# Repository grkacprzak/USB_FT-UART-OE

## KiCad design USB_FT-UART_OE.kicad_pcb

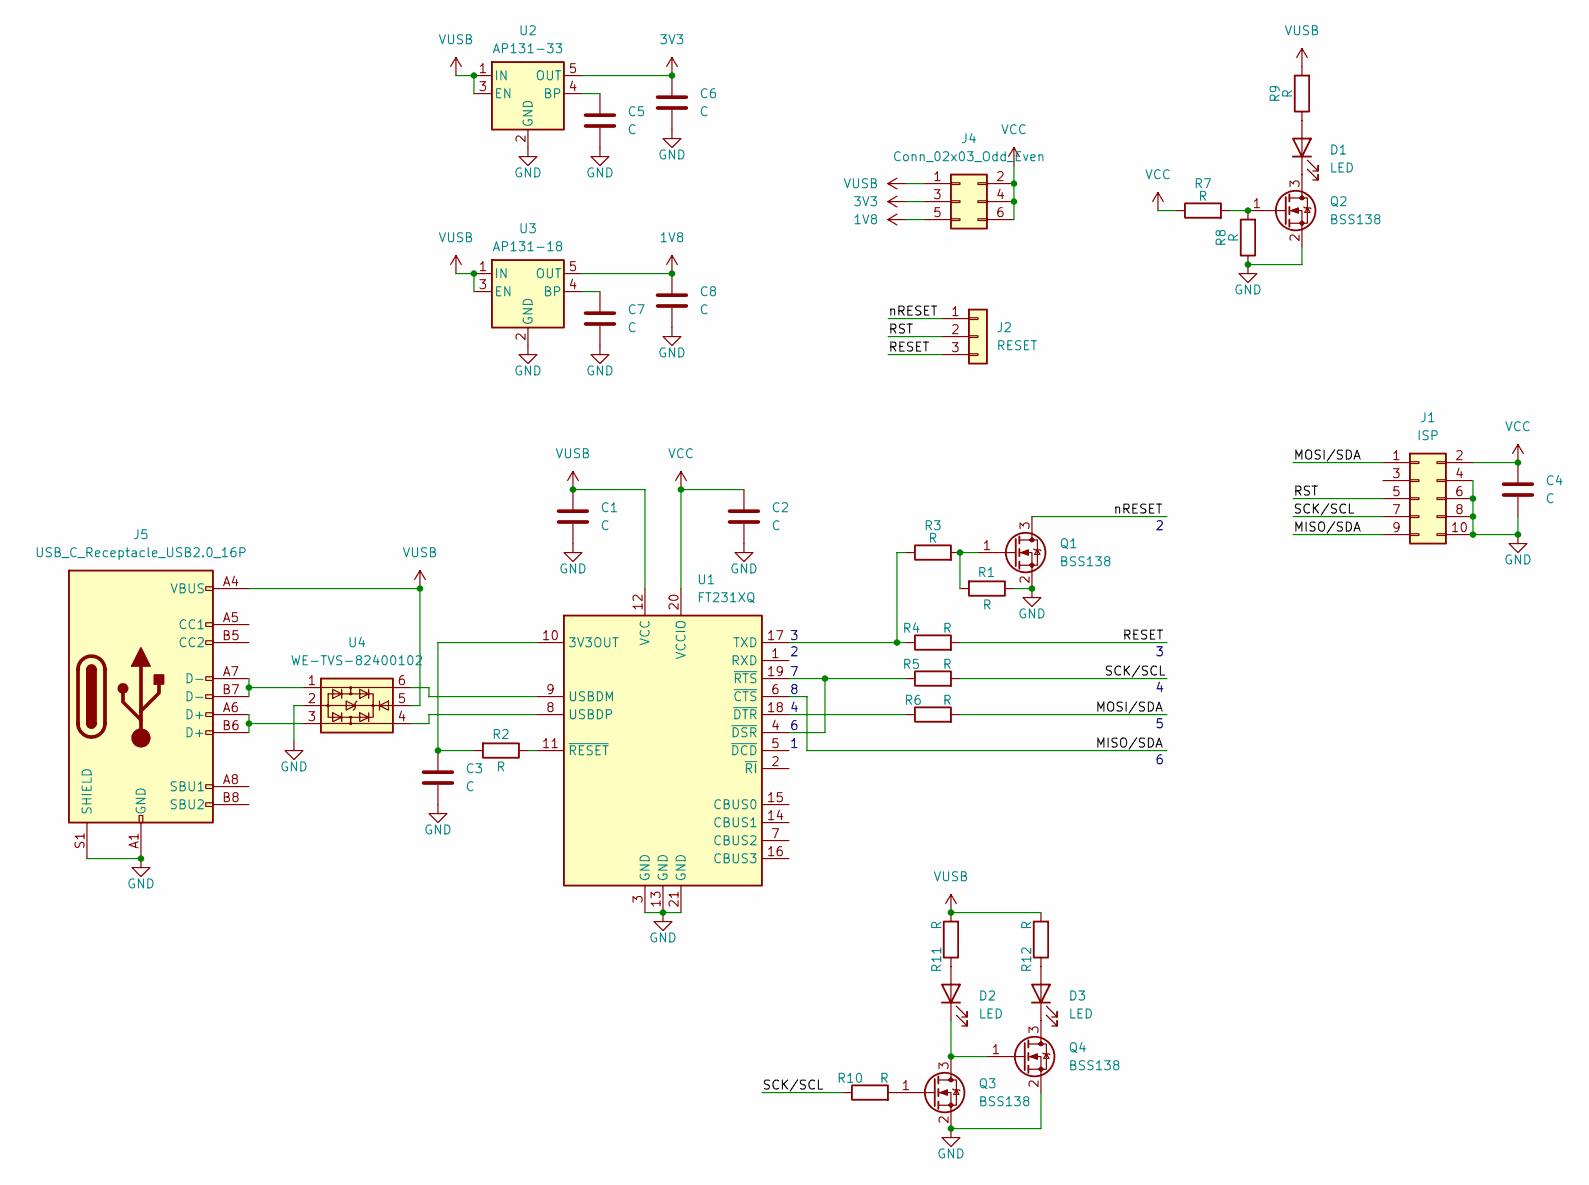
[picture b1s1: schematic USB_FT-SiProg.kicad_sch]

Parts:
C1, C2, C3, C4, C5, C6, C7, C8: C; C_0603_1608Metric
D1, D2, D3: LED; LED_0603_1608Metric
J1: ISP; IDC-Header_2x05_P2.54mm_EDGE
J2: RESET; PinHeader_1x03_P2.54mm_Vertical
J4: Conn_02x03_Odd_Even; PinHeader_2x03_P2.54mm_Vertical
J5: USB_C_Receptacle_USB2.0_16P; USB_C_Receptacle_Wuerth_629722000214
Q1, Q2, Q3, Q4: BSS138; SOT-23
R1, R2, R3, R4, R5, R6, R7, R8, R9, R10, R11, R12: R; R_0603_1608Metric
U1: FT231XQ; QFN-20-1EP_4x4mm_P0.5mm_EP2.5x2.5mm
U2: AP131-33; SOT-23-5
U3: AP131-18; SOT-23-5
U4: WE-TVS-82400102; SOT-23-6

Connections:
1V8: C8.1, J4.5, U3.5 (OUT)
3V3: C6.1, J4.3, U2.5 (OUT)
/MISO/SDA: J1.9, U1.6 (~CTS)
/MOSI/SDA: J1.1, R6.2
/RESET: J2.3, R4.2
/RST: J1.5, J2.2
/SCK/SCL: J1.7, R5.2, R10.1
/nRESET: J2.1, Q1.3 (D)
GND: C1.2, C2.2, C3.2, C4.2, C5.2, C6.2, C7.2, C8.2, J1.4, J1.6, J1.8, J1.10, J5.A1 (GND), J5.A12 (GND), J5.B1 (GND), J5.B12 (GND), J5.S1 (SHIELD), Q1.2 (S), Q2.2 (S), Q3.2 (S), Q4.2 (S), R1.1, R8.1, U1.3 (GND), U1.13 (GND), U1.21 (GND), U2.2 (GND), U3.2 (GND), U4.2
unnamed: D1.2 (A), R9.1
unnamed: D1.1 (K), Q2.3 (D)
unnamed: D2.2 (A), R11.1
unnamed: D2.1 (K), Q3.3 (D), Q4.1 (G)
unnamed: D3.2 (A), R12.1
unnamed: D3.1 (K), Q4.3 (D)
unnamed: J5.A6 (D+), J5.B6 (D+), U4.3
unnamed: J5.A7 (D-), J5.B7 (D-), U4.1
unnamed: Q1.1 (G), R1.2, R3.2
unnamed: Q2.1 (G), R7.2, R8.2
unnamed: Q3.1 (G), R10.2
unnamed: C3.1, R2.2, U1.10 (3V3OUT)
unnamed: R3.1, R4.1, U1.17 (TXD)
unnamed: U1.9 (USBDM), U4.6
unnamed: U1.8 (USBDP), U4.4
unnamed: R5.1, U1.4 (~DSR), U1.19 (~RTS)
unnamed: R6.1, U1.18 (~DTR)
unnamed: R2.1, U1.11 (~RESET)
unnamed: C5.1, U2.4 (BP)
unnamed: C7.1, U3.4 (BP)
VCC: C2.1, C4.1, J1.2, J4.2, J4.4, J4.6, R7.1, U1.20 (VCCIO)
VUSB: C1.1, J4.1, J5.A4 (VBUS), J5.A9 (VBUS), J5.B4 (VBUS), J5.B9 (VBUS), R9.2, R11.2, R12.2, U1.12 (VCC), U2.1 (IN), U2.3 (EN), U3.1 (IN), U3.3 (EN), U4.5

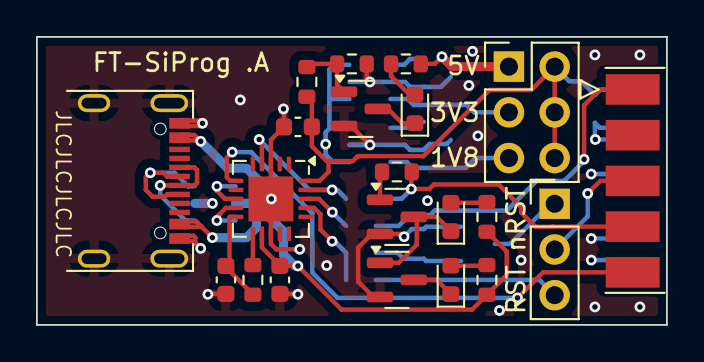
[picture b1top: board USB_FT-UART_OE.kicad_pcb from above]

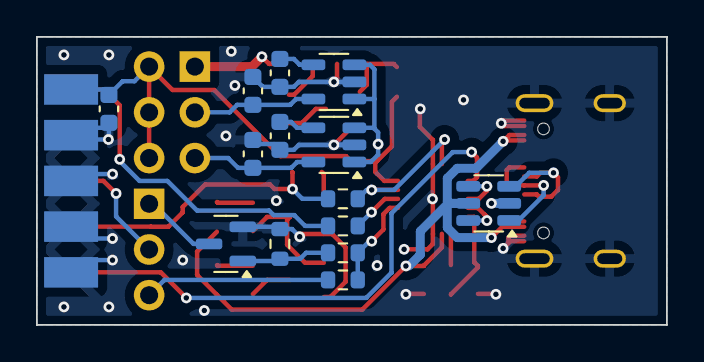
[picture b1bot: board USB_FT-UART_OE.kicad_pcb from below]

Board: 4 copper layers, 35.0 x 16.0 mm, 35 parts (14 on the bottom side), 31 nets.

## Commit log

2024-10-07 version a produced as FTSiProg_USB
2025-10-02 Open Emiter
